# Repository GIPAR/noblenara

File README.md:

# NOBLENARA

### Projeto em desenvolvimento que busca desenvolver, migrar e unificar tecnologias da cadeira de rodas autônoma NARA no ROS2 em uma versão mais atualizada e eficiente

1. O projeto inclui dois subprojetos, "nara-sim" para a simulação e "nara-main" para a cadeira física
2. [Clique aqui](doc/Simulação.md) para abrir o arquivo  "Simulação.md" e ler o tutorial de como utilizar a simulação
3. O desenvolvimento da cadeira física ainda está nas etapas iniciais, para mais detalhes [clique aqui](doc/Cadeira.md) leia o arquivo "Cadeira.md"
4. Paralelamente está sendo criado uma interface web para este projeto, tanto para a cadeira física quanto para a simulação, que pode ser encontrada no repositório [noblenara-ihm](https://github.com/GIPAR/noblenara-ihm)

### Regras de Projeto 🚀📋

Para a plena organização e desenvolvimento do projeto, todos os Commits de novas contribuições devem ser feitas fora do branch principal:

- Cria uma nova branch do repositório com o nome do seu enfoque no projeto
- Ou faça commit no repositório chamado "Desenvolvimento"

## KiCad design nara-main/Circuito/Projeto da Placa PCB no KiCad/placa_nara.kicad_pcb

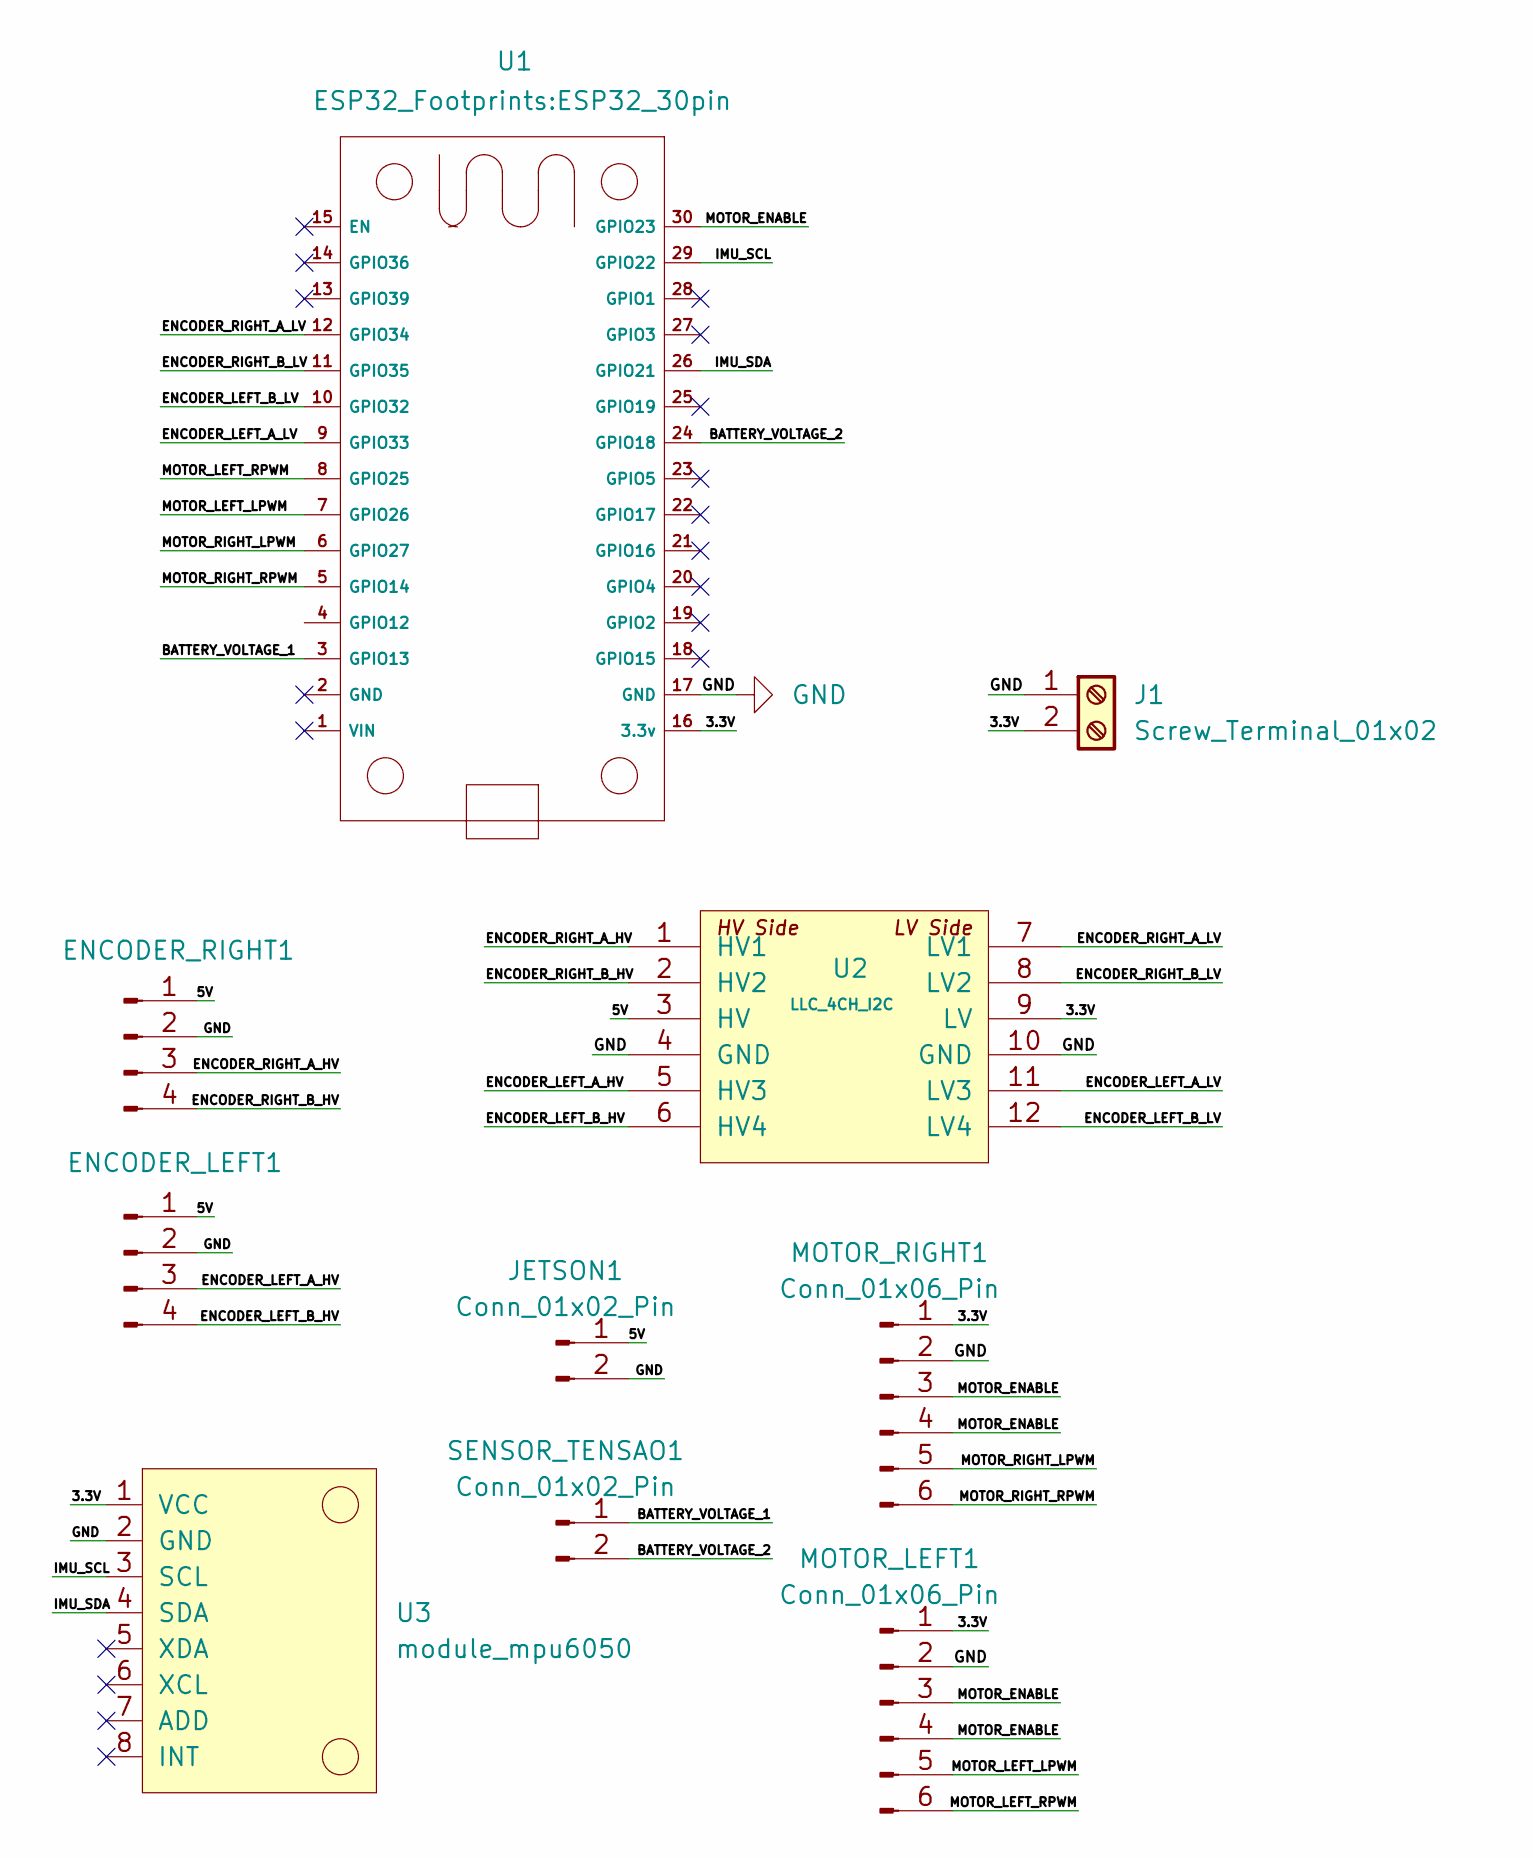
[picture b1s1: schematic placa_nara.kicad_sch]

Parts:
ENCODER_LEFT1: Conn_01x04_Pin; PinHeader_1x04_P2.54mm_Vertical
ENCODER_RIGHT1: Conn_01x04_Pin; PinHeader_1x04_P2.54mm_Vertical
J1: Screw_Terminal_01x02; TerminalBlock_Phoenix_MKDS-1,5-2-5.08_1x02_P5.08mm_Horizont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
JETSON1: Conn_01x02_Pin; PinHeader_1x02_P2.54mm_Vertical
MOTOR_LEFT1: Conn_01x06_Pin; PinHeader_1x06_P2.54mm_Vertical
MOTOR_RIGHT1: Conn_01x06_Pin; PinHeader_1x06_P2.54mm_Vertical
SENSOR_TENSAO1: Conn_01x02_Pin; PinHeader_1x02_P2.54mm_Vertical
U1: ESP32_30pin
U2: LLC_4CH_I2C; LLC_4CH_I2C_MODULE
U3: module_mpu6050

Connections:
/3.3V: J1.2, MOTOR_LEFT1.1, MOTOR_RIGHT1.1, U1.16 (3.3v), U2.9 (LV), U3.1 (VCC)
/5V: ENCODER_LEFT1.1, ENCODER_RIGHT1.1, JETSON1.1, U2.3 (HV)
/BATTERY_VOLTAGE_1: SENSOR_TENSAO1.1, U1.3 (GPIO13)
/BATTERY_VOLTAGE_2: SENSOR_TENSAO1.2, U1.24 (GPIO18)
/ENCODER_LEFT_A_HV: ENCODER_LEFT1.3, U2.5 (HV3)
/ENCODER_LEFT_A_LV: U1.9 (GPIO33), U2.11 (LV3)
/ENCODER_LEFT_B_HV: ENCODER_LEFT1.4, U2.6 (HV4)
/ENCODER_LEFT_B_LV: U1.10 (GPIO32), U2.12 (LV4)
/ENCODER_RIGHT_A_HV: ENCODER_RIGHT1.3, U2.1 (HV1)
/ENCODER_RIGHT_A_LV: U1.12 (GPIO34), U2.7 (LV1)
/ENCODER_RIGHT_B_HV: ENCODER_RIGHT1.4, U2.2 (HV2)
/ENCODER_RIGHT_B_LV: U1.11 (GPIO35), U2.8 (LV2)
/IMU_SCL: U1.29 (GPIO22), U3.3 (SCL)
/IMU_SDA: U1.26 (GPIO21), U3.4 (SDA)
/MOTOR_ENABLE: MOTOR_LEFT1.3, MOTOR_LEFT1.4, MOTOR_RIGHT1.3, MOTOR_RIGHT1.4, U1.30 (GPIO23)
/MOTOR_LEFT_LPWM: MOTOR_LEFT1.5, U1.7 (GPIO26)
/MOTOR_LEFT_RPWM: MOTOR_LEFT1.6, U1.8 (GPIO25)
/MOTOR_RIGHT_LPWM: MOTOR_RIGHT1.5, U1.6 (GPIO27)
/MOTOR_RIGHT_RPWM: MOTOR_RIGHT1.6, U1.5 (GPIO14)
GND: ENCODER_LEFT1.2, ENCODER_RIGHT1.2, J1.1, JETSON1.2, MOTOR_LEFT1.2, MOTOR_RIGHT1.2, U1.17 (GND), U2.4 (GND), U2.10 (GND), U3.2 (GND)

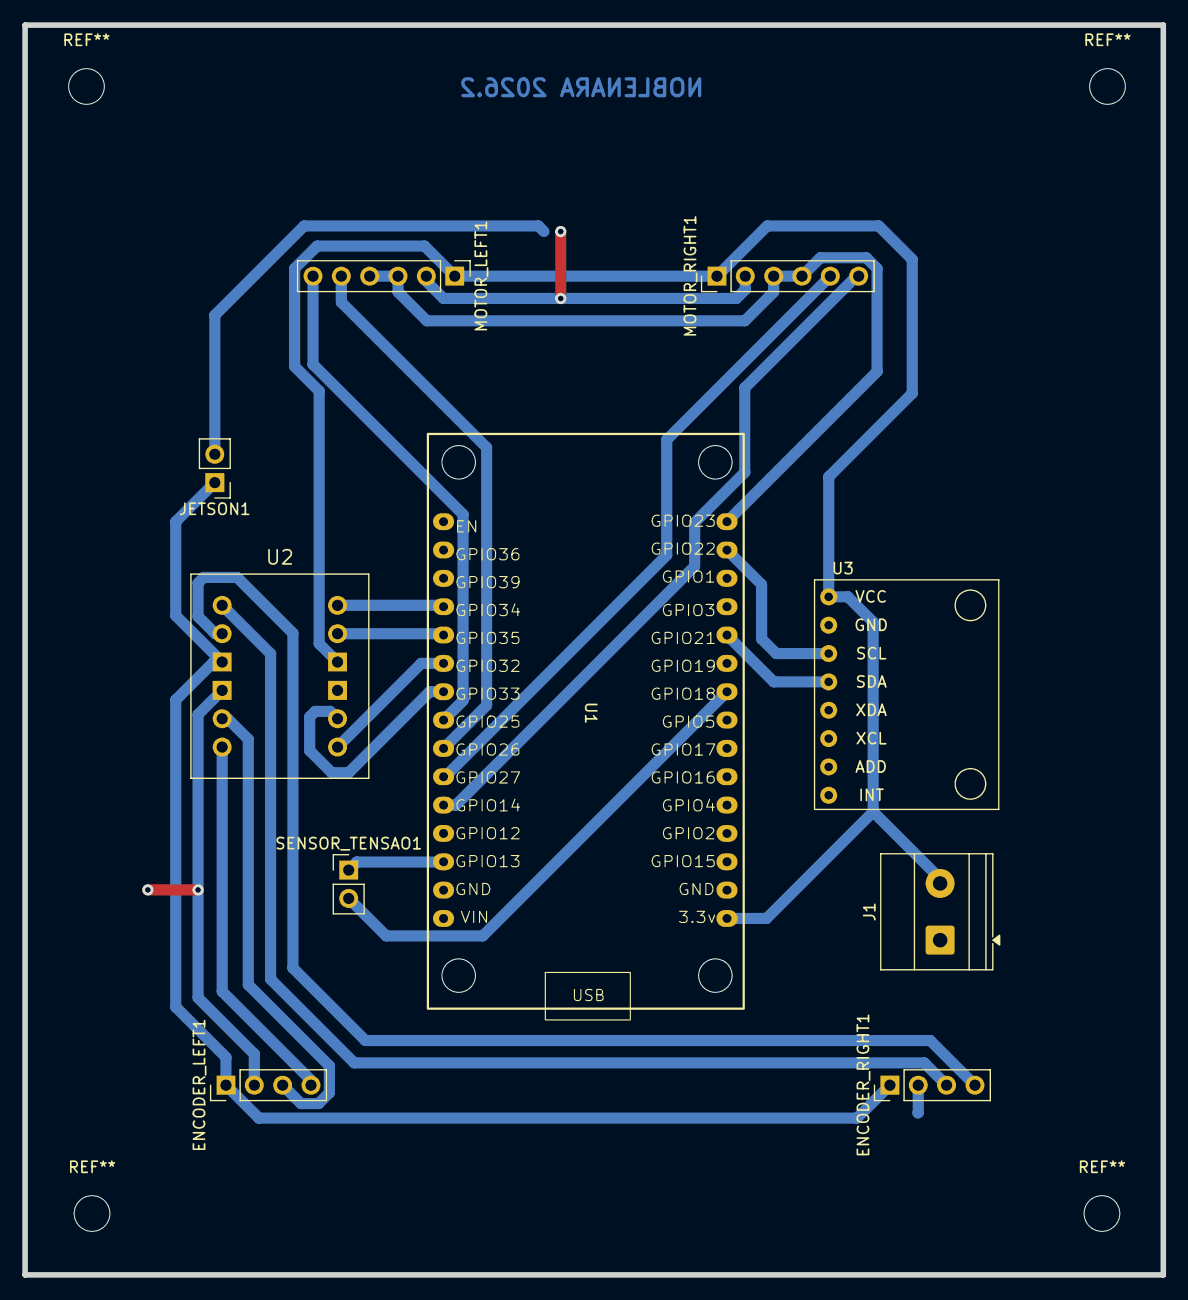
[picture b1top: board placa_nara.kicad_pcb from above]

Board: 2 copper layers, 102.0 x 112.0 mm, 10 parts (0 on the bottom side), 20 nets.

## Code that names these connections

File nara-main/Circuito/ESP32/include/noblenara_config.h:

/**
 * @file noblenara_config.h
 * @brief Configuration file for Noblenara Wheelchair Project
 * @details ROS2 Jazzy + micro-ROS on ESP32-WROOM-32
 *
 * Hardware:
 * - ESP32-WROOM-32 DevKit
 * - 2x ZKP3808 Encoders (600 PPR, quadrature = 2400 counts/rev)
 * - MPU6050 IMU
 * - 2x BTS7960 H-Bridge Motor Controllers
 * - Ottobock B400 Wheelchair Base
 */

#ifndef NOBLENARA_CONFIG_H
#define NOBLENARA_CONFIG_H

//=============================================================================
// DIMENSÕES DO ROBÔ - [METROS]
//=============================================================================
#define WHEEL_DIAMETER 0.350
#define WHEEL_RADIUS (WHEEL_DIAMETER / 2.0)
#define WHEEL_LR_DISTANCE 0.51

#define WHEEL_CIRCUMFERENCE (3.14159265359 * WHEEL_DIAMETER)
#define METERS_PER_COUNT (WHEEL_CIRCUMFERENCE / COUNTS_PER_REV)

//=============================================================================
// CONFIGURAÇÕES DO ENCONDER
//=============================================================================
#define ENCODER_LEFT_A 33
#define ENCODER_LEFT_B 32
#define ENCODER_RIGHT_A 34
#define ENCODER_RIGHT_B 35

#define COUNTS_PER_REV 2400
#define ENCODER_PPR 600

//=============================================================================
// CONFIGURAÇÕES DO MOTOR
//=============================================================================
#define PWM_MAX 100
#define PWM_MIN -PWM_MAX

#define MOTOR_LEFT_LPWM 26
#define MOTOR_LEFT_RPWM 25
#define MOTOR_EN 23
#define MOTOR_RIGHT_LPWM 27
#define MOTOR_RIGHT_RPWM 14

#define lK_P 25.0     // P Left
#define lK_I 30.0  // I
#define lK_D 0.0     // D

#define rK_P 25.0     // P Right
#define rK_I 30.0  // I
#define rK_D 0.0     // D

//=============================================================================
// CONFIGURAÇÕES DA BATERIA
//=============================================================================
#define VOLTAGE_RATIO (4.85 * (4.85 / 3.3))
#define VOLTAGE1_PIN 13
#define VOLTAGE2_PIN 12

//=============================================================================
// CONFIGURAÇÕES MICRO-ROS
//=============================================================================
// #define MICRO_ROS_AGENT_IP    "192.168.1.100"
#define MICRO_ROS_AGENT_PORT 8888

// Taxas de Publicação (ms)
#define WATCHDOG_PUBLISH_RATE 20
#define BATTERY_PUBLISH_RATE 1000
// Telemetria apos o acionamento dos motores. 20 ms = nominalmente 50 Hz.
#define WHEEL_TELEMETRY_PUBLISH_RATE 20

// ROS2 Topic Names
#define ODOM_TOPIC "/noblenara/odom"
#define IMU_TOPIC "/noblenara/imu/data"
#define CMD_VEL_TOPIC "/noblenara/cmd_vel"
#define BATTERY_TOPIC "/noblenara/battery_status"
#define WHEEL_TELEMETRY_TOPIC "/noblenara/wheel_telemetry"

// ROS2 Service Names
#define SetPID_SERVICE "/noblenara/set_pid"

// Timeout do Robô
#define CMD_TIMEOUT_MS 500

#endif

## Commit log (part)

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2025-09-01 README.md
2025-09-02 Delete
2025-09-25 Update chair.launch.py
    adicionado a ponte para os parametros da camera zed atualizado
2025-09-25 Update b400wheelchair.gazebo
    posto o plugin especifico para a Zed 2i
2025-10-06 Update README.md
    corrected both launches
2025-12-05 Adicionado os arquivos da cadeira física
    Adicionado arquivos dos containers
    Arquivos adicionais de notas e modelo 3d
2025-12-11 Adicionando Teleop_Keyboard
    Script básico que precisa ser completado referente ao controlador da simulação na cadeira.
2025-12-11 Update CMakeLists.txt
    Adicionei Script do Teleop_Keyboard no CMakeLists
2025-12-31 trocado o nome do diretório da simulação, movido o arquivo do "tutorial" e mudanças básicas no README
2025-12-31 modificado a descrição/tutorial do projeto e dividido em diferentes arquivos; removido arquivo desnecessário da urdf
2026-02-06 Corrigido a inversão do eixo da cadeira (cmd vel não funcionava como deveria) e outras modificações menores
2026-02-11 Feat: Teleop + Slam
2026-02-13 adicionado/corrigido tf e joint statespublishing
2026-02-19 Modificado código da ESP32 para correto funcionamento do watchdog + adicionado método de publicação em um tópico de mensagens customizadas para a noblenara + Posto Ki = 0 para correto parar das rodas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
    nara-sim -> adicionado um launch file xml para rosbridge_server, web_video_server e rosapi 3 in 1; Útil para a ihm
2026-03-12 Modificado os pinos da ponte h esquerda
    Os pinos 19 e 18 aparentam estar com problema
2026-04-10 Updated SImulação.md e Readme.mds com melhores explicações
2026-05-01 Slam com Rviz, merge do repositório de Giovanne
2026-05-04 NAV2 Commit - Desenvolvimento inicial da navegação autônoma
2026-05-04 Modificado descrição na Simulação.md
2026-05-07 Major Develop
    1. Modificado Angulação do Lidar, possibilitado pelo filtro de laser
    2. Modificado o Box de filtro do Laser
    3. Correções em Slam Params
    4. Modificações de Performance e Eficienceia no Nav2 Params
    5. Adições de Remappings necessárias no Nav2 Launch
2026-05-14 Desenvolvimento inicial do funcionamento de múltiplos robôs em uma única simulação do gazebo;
2026-05-14 Isolado o nome dos nós
2026-05-15 Slam-cadeira física
2026-05-18 Adaptação da ESP para SLAM
2026-05-19 Permitido o uso de múltiplos Slam's de forma conjunta
2026-05-19 Adição do dockerfile atualizado para imagem 'noblenara', Adição do Esquemático/PCB em desenvolvimento, Adição de arquivo contendo informações sobre todos os services presentes na Jetson.
2026-05-19 Pequena correção do .gitignore
2026-05-23 Finder funcionando e injeção de dependencia adicionado
2026-05-25 README da instalação do Slam
2026-05-25 Correções de sintaxe
2026-05-25 text fix
2026-05-25 1. Implementação de navegação autonomâ com multiplos robôs 2. Correção de frame da câmera 3. Modificação do slam config e do frame do mapa, individulizado o mapa para correta separação entre robôs
2026-05-27 1. Atualizado o README 2. Adicionado um segundo arquivo do museu configurado para ser mais leve 3. Modificado nome do nó do Rviz2 para não haver duplicações
2026-05-27 Guia Teleop Atualizado
2026-05-29 Atualizações mínimas do tablet_cam_node
2026-05-29 Atualizado código da ESP32 com a bateria, ros domain e configurações de mensagens
2026-05-29 Pequena correção do código da ESP32
2026-06-01 Trocado o domínio da Zed para 77
2026-06-03 Pequenas modificações de código, incialização das mensagens do imu e aumentado baudrate pra permitir maior frequência de dados
2026-06-03 Trocando a política para volatile e depth
2026-06-06 Permitido inicialização do slam sem o parâmetro "robot_codename", automaticamente nomeia como "alfa". Modiciado Simulação.md
2026-06-17 Corrigido e melhorado código da ESP32
2026-06-20 Noble e Turtle funcionando juntos
2026-06-30 Corrigido README e separado explicações da utilização da Noblenara e Turtlebot
2026-06-30 Modificado Wheel Diameter
2026-06-30 Deletado path antigo de simulação.md
2026-06-30 Recolocação do Lidar no 3D na cadeira
2026-06-30 Teleop sem usar CHMOD, apenas colcon-build
